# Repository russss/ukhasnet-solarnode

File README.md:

# UKHASnet SolarNode

A [ukhasnet node](https://ukhas.net) implementation designed for use as
a remote, solar/lithium battery-powered repeater.

## Features

* STM32 ARM micoprocessor
* CN3083 Li-Ion charge controller
* RFM89[H][W] radio
* Charging and configuration over USB
* Comprehensive battery telemetry:
    * Supply (solar panel) voltage
    * Battery voltage
    * Charge current
    * Charger status
* Breakout for one-wire sensors

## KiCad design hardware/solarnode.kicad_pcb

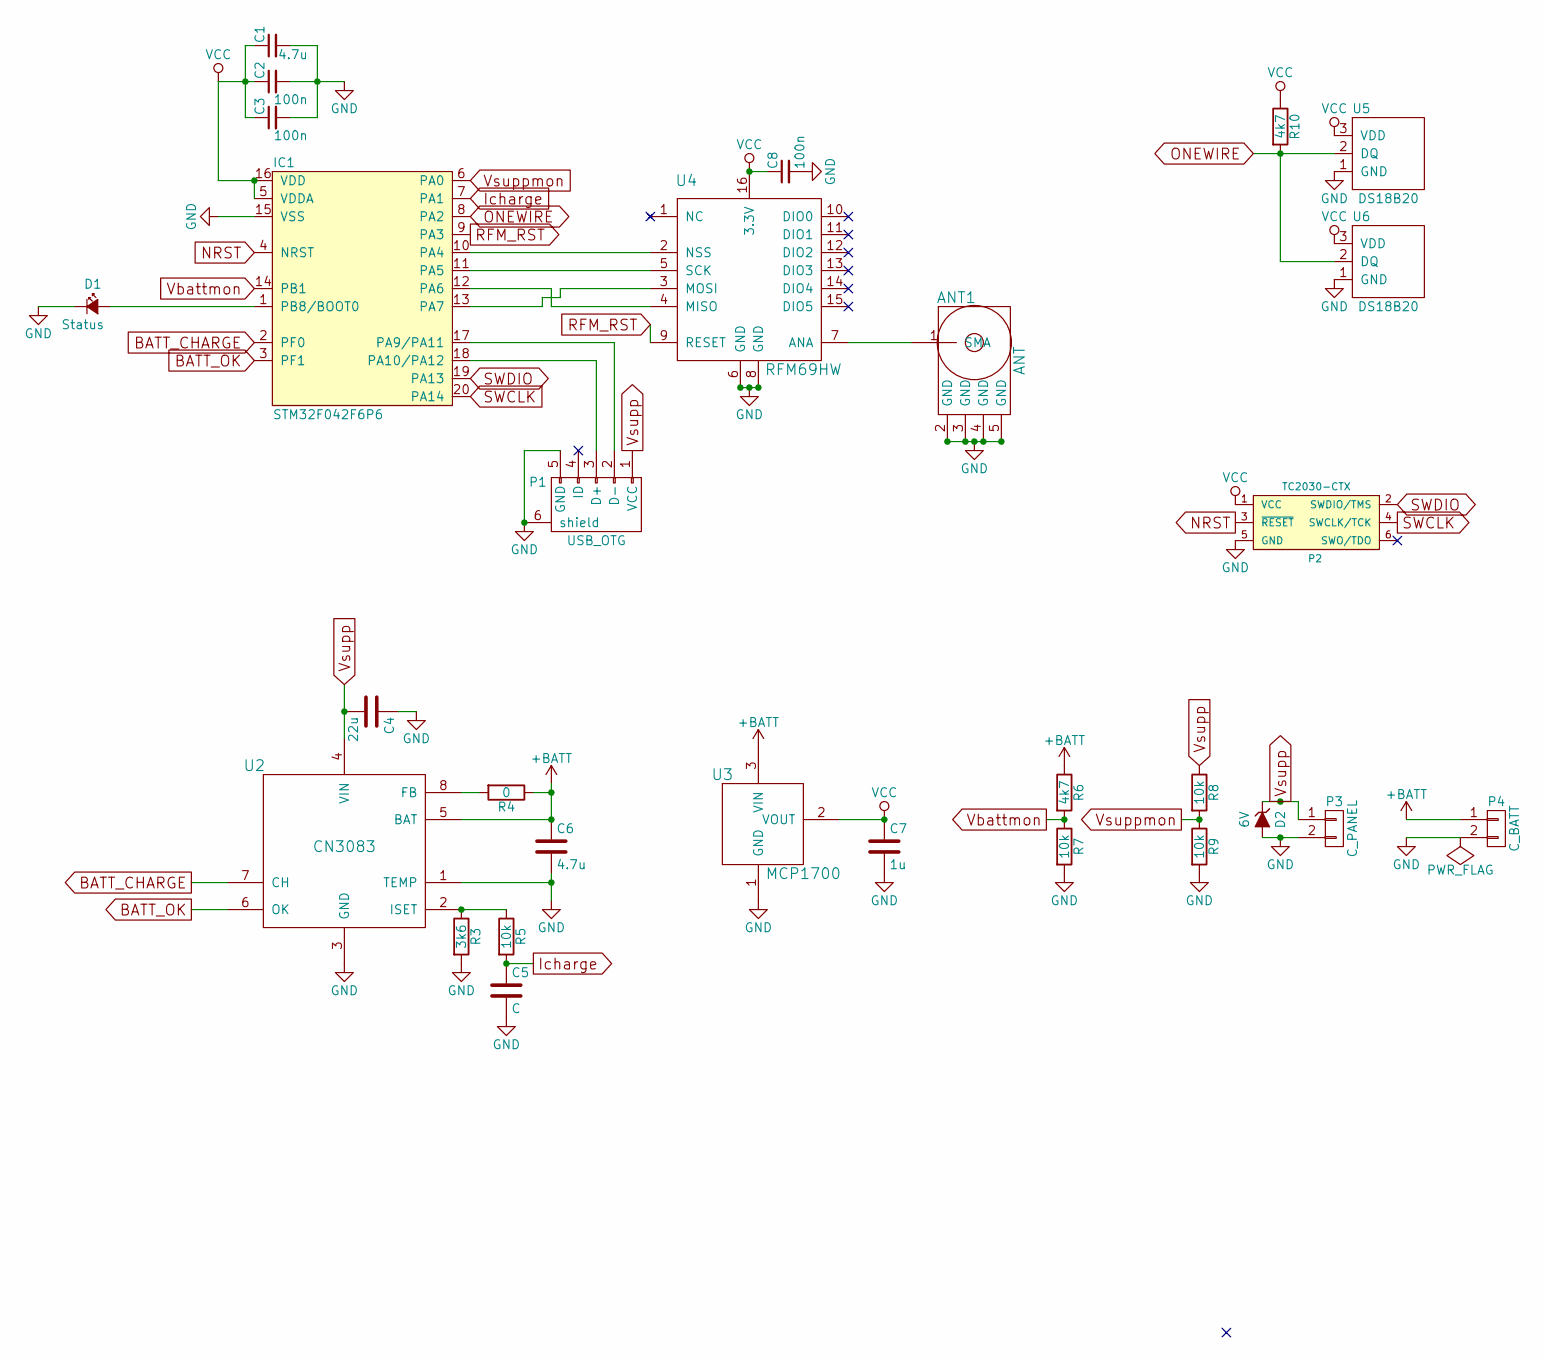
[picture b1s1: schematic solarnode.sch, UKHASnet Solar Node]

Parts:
ANT1: ANT; CON-SMA-EDGE
C1, C6: 4.7u; C_0805
C2, C3, C8: 100n; C_0805
C4: 22u; C_0805
C5: C; C_0805
C7: 1u; C_0805
D1: Status; 0805-LED
D2: 6V; SOD-123
IC1: STM32F042F6P6; TSSOP20; Farnell 2469549
P1: USB_OTG; USB_Micro-B_10103594-0001LF
P2: TC2030-CTX; TC2030-NL_SMALL
P3: C_PANEL; JST-PH-2
P4: C_BATT; JST-PH-2
R3: 3k6; R_0805
R4: 0; R_0805
R5, R7, R8, R9: 10k; R_0805
R6, R10: 4k7; R_0805
U2: CN3083; SOIC-8-EP-CN
U3: MCP1700; SOT-23
U4: RFM69HW
U5, U6: DS18B20; TO-92_Molded_Narrow

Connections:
+BATT: C6.1, P4.1, R4.1, R6.1, U2.5 (BAT), U3.3 (VIN)
BATT_CHARGE: IC1.2 (PF0), U2.7 (CH)
BATT_OK: IC1.3 (PF1), U2.6 (OK)
GND: ANT1.2 (GND), ANT1.3 (GND), ANT1.4 (GND), ANT1.5 (GND), C1.2, C2.2, C3.2, C4.1, C5.2, C6.2, C7.2, C8.2, D1.1 (K), D2.2 (A), IC1.15 (VSS), P1.5 (GND), P1.6 (shield), P2.5 (GND), P3.2, P4.2, R3.2, R7.2, R9.2, U2.1 (TEMP), U2.3 (GND), U2.EP, U3.1 (GND), U4.6 (GND), U4.8 (GND), U5.1 (GND), U6.1 (GND)
Icharge: C5.1, IC1.7 (PA1), R5.2
NRST: IC1.4 (NRST), P2.3 (~RESET~)
unnamed: ANT1.1 (SMA), U4.7 (ANA)
unnamed: D1.2 (A), IC1.1 (PB8/BOOT0)
unnamed: IC1.10 (PA4), U4.2 (NSS)
unnamed: IC1.11 (PA5), U4.5 (SCK)
unnamed: IC1.12 (PA6), U4.4 (MISO)
unnamed: IC1.13 (PA7), U4.3 (MOSI)
unnamed: IC1.17 (PA9/PA11), P1.2 (D-)
unnamed: IC1.18 (PA10/PA12), P1.3 (D+)
unnamed: R3.1, R5.1, U2.2 (ISET)
unnamed: R4.2, U2.8 (FB)
ONEWIRE: IC1.8 (PA2), R10.2, U5.2 (DQ), U6.2 (DQ)
RFM_RST: IC1.9 (PA3), U4.9 (RESET)
SWCLK: IC1.20 (PA14), P2.4 (SWCLK/TCK)
SWDIO: IC1.19 (PA13), P2.2 (SWDIO/TMS)
VCC: C1.1, C2.1, C3.1, C7.1, C8.1, IC1.5 (VDDA), IC1.16 (VDD), P2.1 (VCC), R10.1, U3.2 (VOUT), U4.16 (3.3V), U5.3 (VDD), U6.3 (VDD)
Vbattmon: IC1.14 (PB1), R6.2, R7.1
Vsupp: C4.2, D2.1 (K), P1.1 (VCC), P3.1, R8.1, U2.4 (VIN)
Vsuppmon: IC1.6 (PA0), R8.2, R9.1

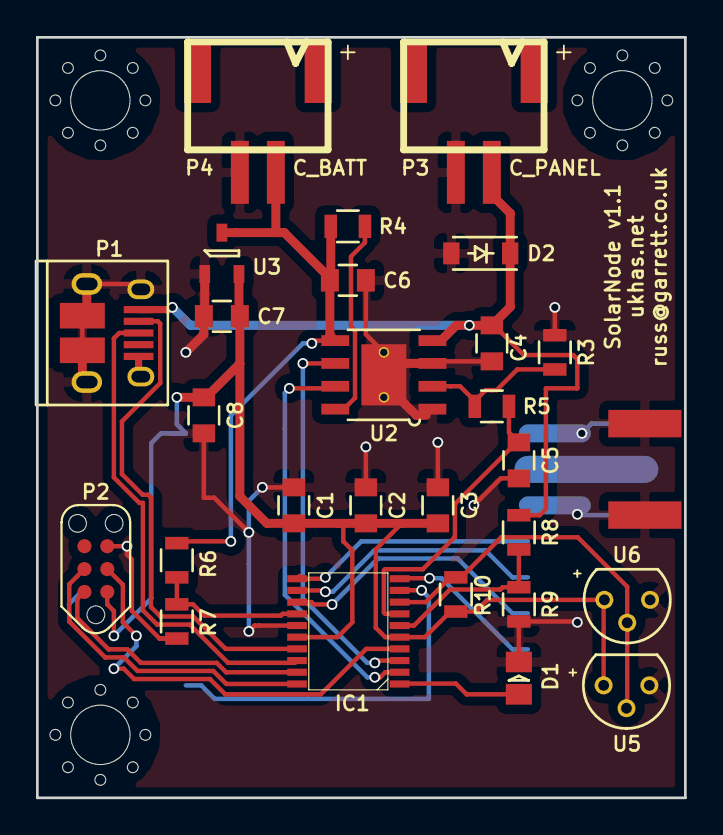
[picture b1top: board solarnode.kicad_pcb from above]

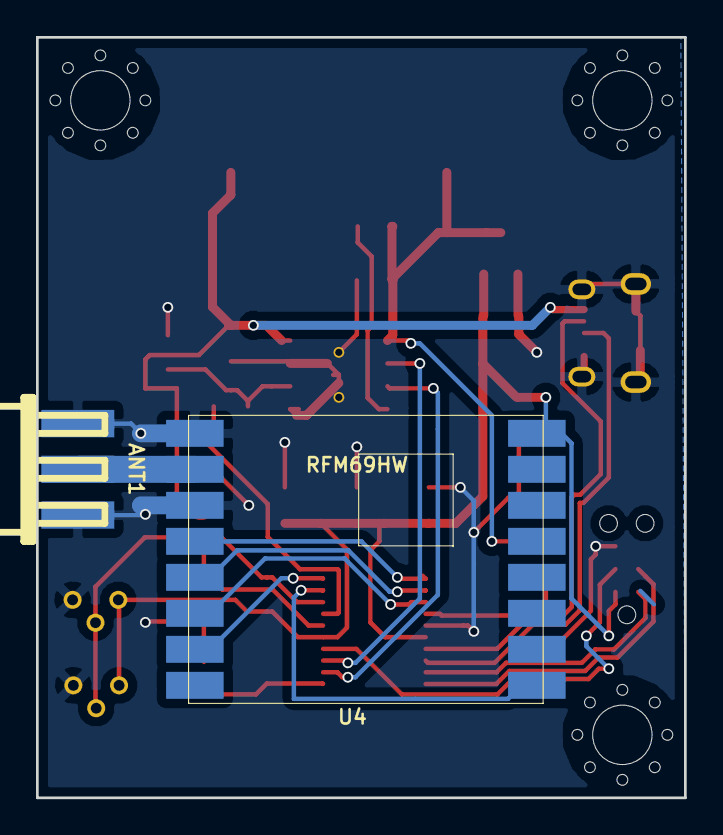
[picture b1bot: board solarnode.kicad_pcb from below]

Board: 2 copper layers, 36.0 x 42.2 mm, 29 parts (2 on the bottom side), 24 nets.

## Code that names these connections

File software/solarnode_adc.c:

#include "ch.h"
#include "hal.h"
#include "solarnode_adc.h"
#include "solarnode_hardware.h"

// PA0 - ADC_IN0 - Vsuppmon
// PA1 - ADC_IN1 - Icharge
// PB1 - ADC_IN9 - Vbattmon
// ADC_IN16 - internal temperature
// ADC_IN17 - Vrefint

// Raw data acquired at a temperature of 30 °C (± 5 °C), VDDA= 3.3 V (± 10 mV)
#define VREFINT_CAL (adcsample_t *)0x1FFFF7BA
// TS ADC raw data acquired at a temperature of 30 °C (± 5 °C), VDDA= 3.3 V (± 10 mV)
#define TS_CAL1     (adcsample_t *)0x1FFFF7B8
// TS ADC raw data acquired at a temperature of 110 °C (± 5 °C), VDDA= 3.3 V (± 10 mV)
#define TS_CAL2     (adcsample_t *)0x1FFFF7C2

#define ADC_RES             4096
#define ADC_NUM_CHANNELS    5

static adcsample_t samples[ADC_NUM_CHANNELS];

static ADCConfig adccfg = {0};
static ADCConversionGroup adcgrpcfg = {
      FALSE,
      ADC_NUM_CHANNELS,
      NULL,
      NULL,
      ADC_CFGR1_RES_12BIT,
      ADC_TR(0, 0),
      ADC_SMPR_SMP_239P5,
      ADC_CHSELR_CHSEL0 | ADC_CHSELR_CHSEL1 | ADC_CHSELR_CHSEL9 | \
          ADC_CHSELR_CHSEL16 | ADC_CHSELR_CHSEL17
};

static float get_vdda_voltage(adcsample_t vrefint) {
     return 3.3 * *VREFINT_CAL / vrefint;
}

static float get_temp(adcsample_t ts_data) {
    return (110.0 - 30.0)/(*TS_CAL2 - *TS_CAL1) * (ts_data - *TS_CAL1) + 30;
}

adc_values_t readADC(void) {
    adc_values_t values;
    adcStart(&ADCD1, &adccfg);
    adcSTM32SetCCR(ADC_CCR_TSEN | ADC_CCR_VREFEN);
    adcStartConversion(&ADCD1, &adcgrpcfg, samples, 1);
    chThdSleepMilliseconds(500);
    adcStop(&ADCD1);

    values.vdda_voltage = get_vdda_voltage(samples[4]);
    values.supply_voltage = ((float)samples[0] / ADC_RES * values.vdda_voltage) / VSUPPMON_DIVIDER;
    values.batt_voltage = ((float)samples[2] / ADC_RES * values.vdda_voltage) / VBATTMON_DIVIDER;
    values.charge_current = ((float)samples[1] / ADC_RES * values.vdda_voltage) / ICHARGE_DIVIDER;
    values.internal_temp = get_temp(samples[3]);
    return values;
}

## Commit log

2016-04-17 Initial hardware design
2016-04-17 README
2016-04-17 BOM CSV
2016-04-17 Fix open-drain pull-ups to be actual pull-ups
2016-04-17 Update gitignore
2016-05-18 Chibios firmware. USB working.
2016-05-19 Add CN3083 state pins
2016-05-19 Reduce stack size. Fix inverted charge/OK.
2016-05-20 v1.0 Stencil
2016-05-20 Version 1.1
    - Fix incorrect RFM69 SPI wiring
    - Remove unneeded pullup resistors on CN3083 open-drain outputs
    - Fix silk text sizing so it's actually readable
2016-05-20 Add PCB layout to readme
2016-05-20 Remove unneeded boot jumper
2016-05-29 Save Nearly 7kB Code Size With This One Weird Trick
2016-05-29 More code size optimisations
2016-05-29 Initial user config code
2016-05-29 Initial onewire code
2016-05-29 Fix line endings
2016-05-29 Include onewire driver directly
2016-06-04 Board config tweaks
2016-06-04 Shell improvements
2016-06-04 Initial RFM69 driver
2016-06-04 Misc other tweaks
2016-06-04 Version 1.1 hardware + stencil
2016-06-05 Allocate shell thread statically
2016-06-05 LED blinker thread
2016-06-05 More RFM69 improvements
2016-06-05 More RFM69 work. Now appears to be transmitting but isn't.
2016-06-05 Improve RFM69 diagnostics in shell
2016-06-08 Current (broken) RFM69 state
2016-06-10 Working RFM69, plus other updates
2016-06-11 Working flash code
2016-06-11 Remove unused option byte code
2016-06-11 Add nano.specs to shrink standard library
2016-06-11 Remove -Os for debuggability
2016-06-11 More configurability, add data to tx
2016-06-11 Initial zombie mode code
2016-06-11 Pack charge status into one byte
2016-06-11 Zombie mode configuration flag
2016-06-11 Fix zombie logic bug
2016-06-12 Repeat logic
2016-06-12 todo update
2016-06-12 Enable stack checking
2016-06-12 Increase RFM69 stack size
2016-06-12 Initial output power setting logic
2016-06-13 Use 2 decimal places for all voltages
2016-06-15 Increase default low battery voltage to 3.9V
2016-06-15 Increase max USB power to 512mA to reflect charge current
2016-06-16 Working 1-wire temperature reading
2016-06-16 Add chibios as submodule
2016-06-16 Check onewire CRC
2016-06-16 Add 1-wire retry logic
    because the 1-wire implementation is not bulletproof
2016-06-16 Remove debug function. Add watchdog, only in non-debug mode
2016-06-16 Version code
2016-06-18 RFM69 high-power settings and tweaks
2016-08-31 Some old uncommitted changes
2016-08-31 Remove unused onewire code
2016-09-03 Fix prototype
2016-09-03 Delay before initialising RFM69 to attempt to reduce inrush
2016-09-03 Display chip serial number in usb info
2016-09-03 Tweaks to transmit logic. Send version in comment on b packet
2016-09-03 DFU upgrade from USB (not working)
2016-09-03 Version bump to v0.2
2016-09-03 Fix compile errors
2016-09-03 Shell config tweaks
2016-09-03 More sensible default config
2016-09-03 Better error checking in shell
2016-09-03 Set default repeat count to 3
2016-09-12 Format RSSI threshold correctly
